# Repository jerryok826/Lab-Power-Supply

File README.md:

# Lab Power Supply

## Project Description
I always thought that most laborary power supplies (LPS) take up to much bench space. This design is just 2.5 inches by 5.5 inches and runs off a wall wart or it can be powered from a lithium battery pack. The unit's specs are 0 to 15 volts output with a maximum output current of 1.5 amps. It has two output adjustable voltage presets with defaults of 5 and 3.3 volts. It has two rotary encoders, one for voltage control and the other for current limiting. Pressing an encoder button will change it's adjustement range. There is one additional button for output enable. The LPS can also be controlled remotely via USB using ModBus. There is also a realtime analog current bar graph on the oled display.

The control processor is a stm32f103c8t6, an Arm Cortex-M3 MCU with 64 Kbytes of flash memory and a 72 MHz CPU. The current code runs on libopencm3 and FreeRTOS. The display is a 256x128 OLED display. It is driven by uGui software. The unit is composed of two boards. The top board is the control and display board. The board below is the regulator board. The regulator board is composed of a low voltage drop linear regulator and a highly efficient switching regulator. Because of the combined efficiency of the switching and linear regulator not much of a heat sink is required. To reduce the noise generated by the switcher to a minimum, the switcher has large imput capacitors and a 3KHz loop pass filter on its output feeding the linear regulator. The switcher output voltage set to maintain a two voltage drop across the linear regulator.
### Project Status
The project is basically complete. I am working on converting the design to Kicad and STM32 IDE Cube. Also I'm thinking abouting redoing the display board with a RP2040 running MicroPython. This should make it easy for the end user to add their own features. For example, adding WIFI control support.

## Design Files
### Electrical Design Files
This project was initially designed with Altium Designer and is now being updated with Kicad 7.X The control software is C code runing on FreeRTOS.

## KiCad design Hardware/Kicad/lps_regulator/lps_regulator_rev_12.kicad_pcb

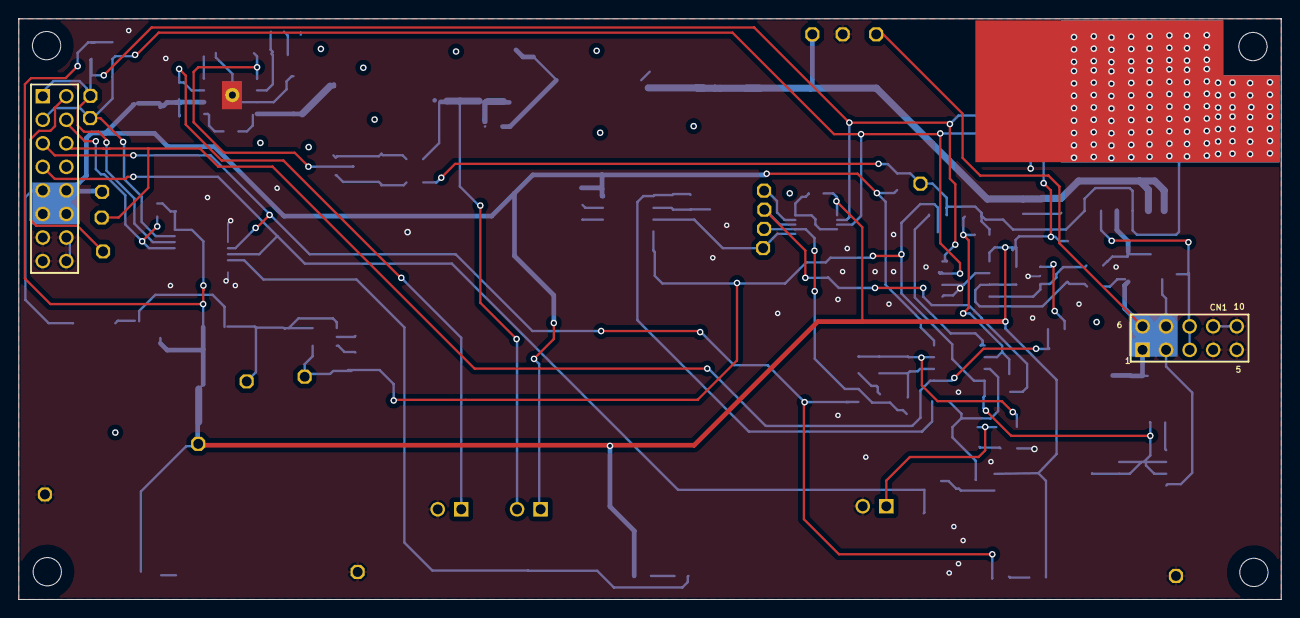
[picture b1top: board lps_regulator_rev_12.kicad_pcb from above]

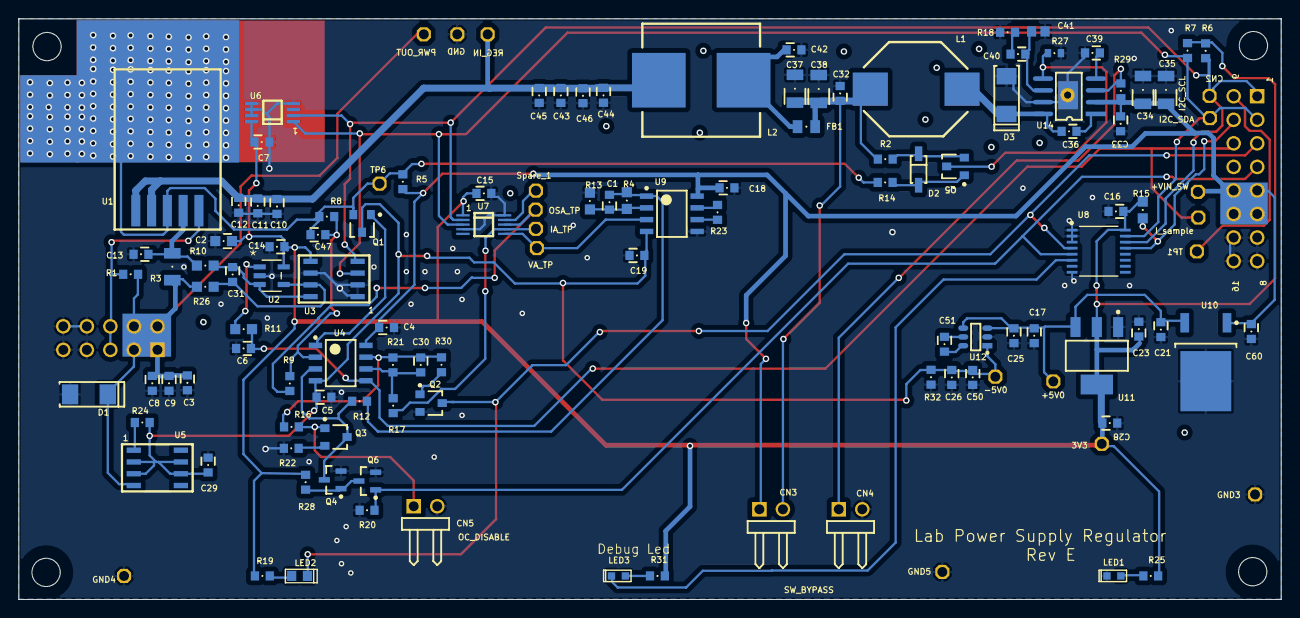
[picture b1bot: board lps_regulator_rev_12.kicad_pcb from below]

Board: 2 copper layers, 136.2 x 62.6 mm, 130 parts (109 on the bottom side), 55 nets.

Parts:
3V3: TestPoint_BLK; TestPoint-TH 42 mil
+5V0: TestPoint_BLK; TestPoint-TH 42 mil
+VIN_SW: TestPoint_BLK; TestPoint-TH 42 mil
-5V0: TestPoint_BLK; TestPoint-TH 42 mil
C1: 100pF; CAPC0603(1608)_N
C2: 0.1uF; CAPC0603(1608)_M
C3, C4, C5, C7, C12, C13, C14, C15, C16, C18, C19, C21, C23, C26, C29, C31, C32, C36, C42, C44, C47: 0.1uF; CAPC0603(1608)_N
C6, C8, C9, C10, C11, C17, C25, C28, C30, C43, C45, C50: 10uF; CAPC0603(1608)_N
C33, C39: 0.01uF; CAPC0603(1608)_N
C34, C35: 4.7uF; CAPC1206(3216)_N
C37, C38: 47UF; CAPC1206(3216)_N
C40: 150pF; CAPC0603(1608)_N
C41: 8.2nF; CAPC1608X87X35ML15T15
C46, C51, C60: 1uF; CAPC0603(1608)_N
CN1: Header 5X2A; HDR2X5_CEN
CN2: Header 8X2A; HDR2X8_CEN
CN3, CN4, CN5: Header 2H; HDR1X2H
D1, D3: B340A; DO-214AC
D2: 1N4448W-E3-18; SOD123
FB1: 300 Ohm @ 100MHz, 0805; RESC0805(2012)_N
GND, GND3, GND4, GND5: TestPoint_BLK; TestPoint-TH 42 mil
I2C_SCL, I2C_SDA: TestPoint_BLK; TestPoint-TH 42 mil
IA_TP: TestPoint_BLK; TestPoint-TH 42 mil
I_sample: TestPoint_BLK; TestPoint-TH 42 mil
L1: SSR1028 6.8uH; SRU1028
L2: SSR1210 100uH; SRR1210
LED1, LED3: 0603 LED; SM-LED-0603
LED2: G; SM-LED-0603
OSA_TP: TestPoint_BLK; TestPoint-TH 42 mil
PWR_OUT: TestPoint_BLK; TestPoint-TH 42 mil
Q1, Q5: MMBT2907A; SOT23
Q2, Q3: MMBT3904; SOT23
Q4, Q6: BSS123TA; SOT23-3L
R1, R23, R24: 100; RESC0603(1608)_N
R2, R5, R6, R7, R8, R9, R14, R20, R28, R29: 10K; RESC0603(1608)_N
R3: 0.33; RESC1206(3216)_N
R4, R13, R15: 10k; RESC0603(1608)_M
R10, R11, R26: 10K; RESC0603(1608)_M
R12, R16, R17, R19, R22, R25, R30, R31, R32: 1.0K; RESC0603(1608)_N
R18: 33K; RESC0603(1608)_N
R21: 100K; RESC0603(1608)_N
R27: 10K; RESC0603(1608)_L
REG_IN: TestPoint_BLK; TestPoint-TH 42 mil
Spare_1: TestPoint_BLK; TestPoint-TH 42 mil
TP1, TP6: TestPoint_BLK; TestPoint-TH 42 mil
U1: TPS7A4515KTTR
U2: INA180A1; SOT-23-5_MC
U3: INA219
U4, U9: OPA2320; SOIC-8_NoPad
U5: LM334
U6: mcp9808; 8MSOP
U7: mcp4728; MCP4728
U8: TCA9534APWR; TCA9534APWR-Footprint-1
U10: TO-252_N
U11: LD1117S33; DSO-G3
U12: LM2776; SOt-23-6
U14: TPS54331
VA_TP: TestPoint_BLK; TestPoint-TH 42 mil

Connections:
3V3: 3V3.1, C2.1, C7.1, C14.1, C15.1, C16.1, C23.1, C28.1, R6.1, R7.1, R15.2, R19.1, R25.1, R28.1, R31.1, U2.5, U3.5, U6.8, U7.1, U8.16, U11.2, U11.4
+5V0: +5V0.1, C17.1, C21.1, C25.1, U10.3, U11.3, U12.3, U12.4
+VIN_SW: +VIN_SW.1, C4.1, C18.1, C33.1, C34.1, C35.1, C60.1, CN2.5, CN2.6, CN2.13, CN2.14, CN3.1, R5.1, R29.1, U4.8, U9.8, U10.1, U14.2
-5V0: -5V0.1, C5.1, C19.2, C26.1, C29.2, C50.1, Q1.3, R24.2, R32.1, U4.4, U5.2, U5.3, U5.6, U5.7, U9.4, U12.1
/INT: CN2.10, R15.1, U8.13
/RST: CN2.9, TP1.1
Current_Limit: CN2.3, LED2.2, Q2.3, U8.4
Debug_LED: LED3.2, U8.6
GND: C2.2, C3.2, C4.2, C5.2, C6.2, C7.2, C8.2, C9.2, C10.2, C11.2, C12.2, C13.2, C14.2, C15.2, C16.2, C17.2, C18.2, C19.1, C21.2, C23.2, C25.2, C26.2, C28.2, C29.1, C32.2, C33.2, C34.2, C35.2, C37.2, C38.2, C39.2, C41.1, C42.2, C43.2, C44.2, C45.2, C46.2, C50.2, C60.2, CN1.4, CN1.5, CN1.9, CN1.10, CN2.7, CN2.8, CN2.15, CN2.16, CN4.2, CN5.2, D1.1, D3.1, GND.1, GND3.1, GND4.1, GND5.1, LED1.2, Q2.2, Q4.2, Q6.2, R13.1, R18.2, R20.2, R22.2, R27.2, R32.2, U2.2, U3.1, U3.2, U3.6, U6.4, U6.5, U6.6, U6.7, U7.4, U7.10, U8.1, U8.2, U8.3, U8.8, U9.5, U10.4, U11.1, U12.2, U14.7, U14.9
I2C_SCL: CN2.1, I2C_SCL.1, R6.2, U3.4, U6.2, U7.2, U8.14
I2C_SDA: CN2.2, I2C_SDA.1, R7.2, U3.3, U6.1, U7.3, U8.15
IA_TP: IA_TP.1, R17.1, U7.7
I_Sample: C6.1, CN2.11, I_sample.1, R11.2, U4.5
NetC1_1: C1.1, R4.1, R13.2, U9.2
NetC17_1: C51.1, U12.5
NetC17_2: C51.2, U12.6
NetC30_1: C30.1, R16.1, R21.2, R30.2, U4.7
NetC30_2: C30.2, R17.2, R21.1, U4.6
NetC31_1: C31.1, R10.1, U2.3, U3.8
NetC31_2: C31.2, R26.1, U2.4, U3.7
NetC32_1: C32.1, C37.1, C38.1, CN3.2, FB1.1, L1.2, R2.1
NetC36_1: C36.1, U14.1
NetC36_2: C36.2, D3.2, L1.1, U14.8
NetC39_1: C39.1, U14.4
NetC40_1: C40.1, C41.2, U14.6
NetC40_2: C40.2, R18.1
NetC42_1: C42.1, FB1.2, L2.1
NetC47_1: C47.1, Q1.2, R5.2, R8.1, R14.2, TP6.1, U1.3, U1.6
NetC47_2: C47.2, R8.2, R9.1, U4.2
NetCN1_3: CN1.3, CN1.8, R1.2, U1.5
NetCN4_1: CN4.1, R29.2, U14.3
NetCN5_1: CN5.1, Q3.1, R16.2
NetD2_1: D2.1, Q5.1, R14.1
NetD2_2: D2.2, Q5.2, R2.2
NetLED1_1: LED1.1, R25.2
NetLED2_1: LED2.1, R19.2
NetLED3_1: LED3.1, R31.2
NetQ1_1: Q1.1, U4.1
NetQ2_1: Q2.1, R30.1
NetQ3_2: Q3.2, R22.1
NetQ3_3: Q3.3, Q4.3, R12.2, U4.3
NetQ4_1: Q4.1, Q6.3, R28.2
NetQ5_3: Q5.3, R27.1, U14.5
NetR11_1: R11.1, U2.1
NetR23_1: R23.1, U9.6
NetR23_2: R23.2, U9.7
NetR24_1: R24.1, U5.1
NetSpare_1_1: Spare_1.1, U7.9
OUTPUT_ENB: CN2.4, Q6.1, R20.1, U8.5
Pwr_Out: C3.1, C8.1, C9.1, CN1.1, CN1.2, CN1.6, CN1.7, D1.2, PWR_OUT.1, R1.1, R3.2, R26.2, U5.4
Pwr_Out_Sample: C13.1, R3.1, R10.2, U1.4
REG_VIN: C10.1, C11.1, C12.1, C43.1, C44.1, C45.1, C46.1, L2.2, REG_IN.1, U1.1, U1.2
VA_TP: U7.6, U9.3, VA_TP.1
VA_TP_GAIN: C1.2, R4.2, R12.1, U9.1
V_offset_adj: OSA_TP.1, R9.2, U7.8

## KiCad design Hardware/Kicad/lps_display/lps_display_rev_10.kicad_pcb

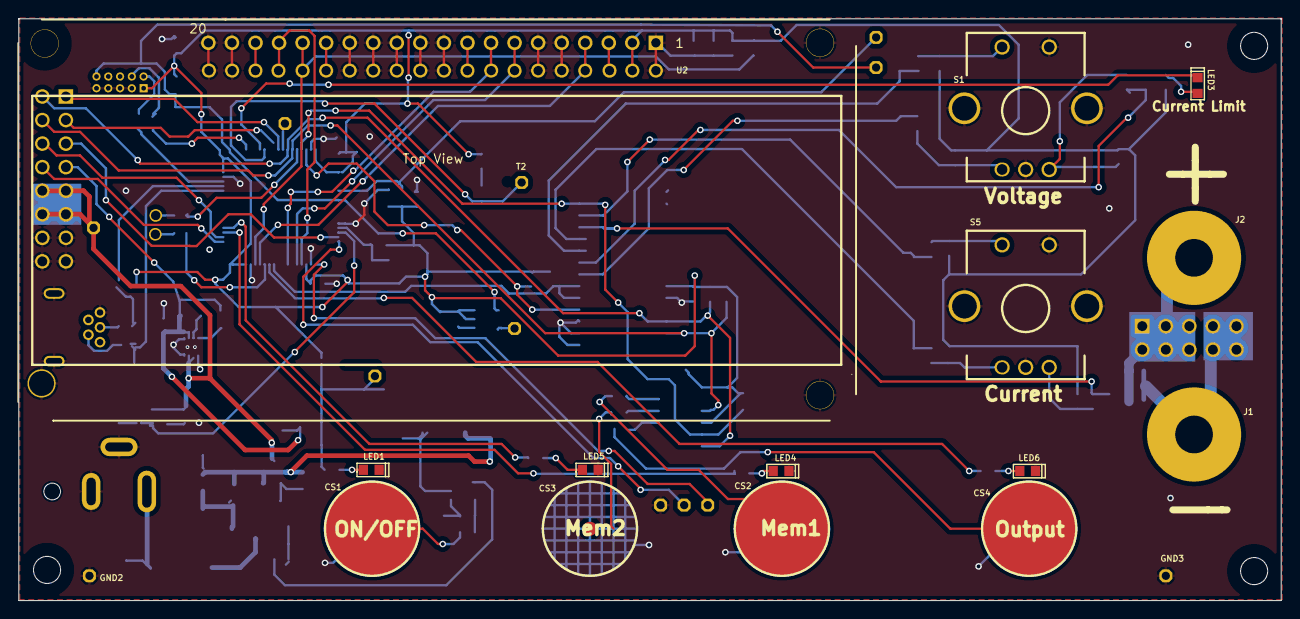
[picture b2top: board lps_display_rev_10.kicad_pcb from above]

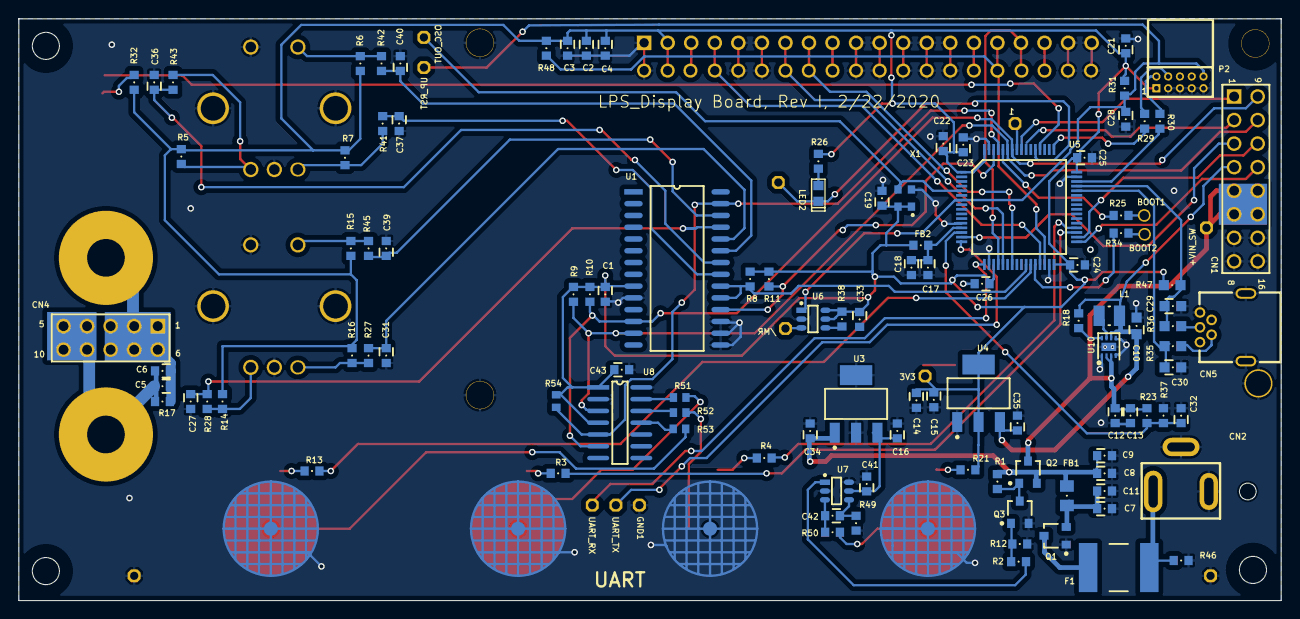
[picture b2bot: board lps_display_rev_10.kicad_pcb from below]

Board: 2 copper layers, 136.1 x 62.7 mm, 137 parts (112 on the bottom side), 84 nets.

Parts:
1, 3V3: TestPoint-TH 35 mil
+VIN_SW: TestPoint-TH 35 mil
/MR: TestPoint-TH 35 mil
BOOT1, BOOT2: TP; TestPoint-TH 40 mil
C1, C4, C6, C8, C11, C13, C15, C18, C19, C21, C23, C24, C25, C26, C27, C31, C32, C33, C34, C35, C36, C37, C39, C40, C41, C42, C43: 0.1uF 0603 50V; CAPC0603(1608)_N
C2, C3, C5, C7, C9, C12, C14, C16, C17, C22: 10uF; CAPC0603(1608)_N
C10: 22uF; CAPC0603(1608)_M
C28: 1uF; CAPC0603(1608)_N
C29, C30: 33pF; CAPC0603(1608)_M
CN1: Header 8X2A; HDR2X8_CEN
CN2: PJ-050AH
CN4: Header 5X2A; HDR2X5_CEN
CN5: Mini-USB RA Type B; USB-MINI-B - 2A
CS1, CS2, CS3, CS4: Cap_Sense_Pad; CAP_TOUCH_ROUND
F1: 2920L500/16MR; 2920 Fuse
FB1: 300 Ohm @ 100MHz, 0806; RESC0805(2012)_M
FB2: BLM18RK601SN1D; RESC0603(1608)_N
GND1, GND2, GND3: TestPoint-TH 35 mil
J1, J2: banana_jack1; Banana_jack1
L1: 2.2uH; INDC2520X10N
LED1, LED2, LED3, LED4, LED5, LED6: G; SM-LED-0603
OSC_OUT: TestPoint-TH 35 mil
P2: jtag_debug
Q1, Q2: DMP3099L-7; SOT23
Q3: MMBT3904; SOT23
R1, R2, R5, R6, R7, R8, R9, R10, R11, R12, R14, R15, R16, R17, R21, R27, R28, R38, R41, R42, R43, R45, R48: 4.7K; RESC0603(1608)_N
R3, R4, R13, R23, R26, R32, R37, R46, R49, R50: 1.0K; RESC0603(1608)_N
R18, R25, R34: 100K; RESC0603(1608)_N
R29, R30: 100; RESC0603(1608)_N
R31: 10K 1%; RESC0603(1608)_N
R35, R36: 22; RESC0603(1608)_M
R47: 1.54K; RESC0603(1608)_M
R51, R52, R53, R54: 5.1K; RESC1608X55X30NL15T15
S1, S5: rotary encoder
T2: TestPoint-TH 35 mil
U1: MCP23017; SOIC28
U2: OLED Display; oled_graphic_256X64
U3: TPS7B6933QDCYRQ1; SOT-223
U4: 3.3V; DSO-G3
U5: STM32F103RCT6; LQFP64
U6: TPS3808G33; SOt-23-6
U7: AT42QT1012; SOt-23-6
U8: AT42QT1070; SOP14
U10: TPS62173DSGT; WSON(8) 2mm x 2mm
UART_RX: TestPoint-TH 35 mil
UART_TX: TestPoint-TH 35 mil
UP_RST: TestPoint-TH 35 mil
X1: 8.0000MHZ; ECS-TXO-2520-33-160-AN-TR-Footprint-1

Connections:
3V3: 3V3.1, C1.1, C2.1, C3.1, C4.1, C14.1, C15.1, C19.1, C21.1, C22.1, C23.1, C24.1, C25.1, C26.1, C33.1, C43.1, FB2.1, P2.1, R5.2, R6.2, R7.2, R8.2, R9.2, R10.2, R11.2, R14.2, R15.2, R16.2, R21.2, R26.2, R31.1, R32.2, R38.2, R47.1, R48.2, R54.2, U1.9, U2.2, U4.2, U4.4, U5.1, U5.19, U5.32, U5.48, U5.64, U6.5, U6.6, U8.1, U8.4, X1.1, X1.4
5V0: C10.1, C35.1, CN1.4, L1.2, R18.1, U4.3, U10.6
8MH_XTAL_IN: OSC_OUT.1, U5.5, X1.3
+VIN: C8.1, C9.1, C34.1, FB1.2, Q2.2, R1.2, U3.1
+VIN_SW: +VIN_SW.1, C12.1, C13.1, CN1.5, CN1.6, CN1.13, CN1.14, Q2.3, R23.2, U10.2, U10.3
/CAP_T_INT: R54.1, U1.27, U5.61, U8.5
/INT: R8.1, U1.19, U1.20, U5.26
/RST_MCP23017: R11.1, U1.18, U5.62
/RST_OLED: R48.1, U2.16, U5.30
Current_Limit: CN1.11, U5.34
D/C_OLED: U2.4, U5.29
DEBUG_LED: LED2.2, T2.1, U5.53
GND: C1.2, C2.2, C3.2, C4.2, C7.2, C8.2, C9.2, C10.2, C11.2, C12.2, C13.2, C14.2, C15.2, C16.2, C17.2, C18.2, C19.2, C21.2, C22.2, C23.2, C24.2, C25.2, C26.2, C27.2, C28.2, C29.2, C30.2, C31.2, C32.2, C33.2, C34.2, C35.2, C36.2, C37.2, C39.2, C40.2, C41.2, C43.2, CN1.7, CN1.8, CN1.15, CN1.16, CN2.2, CN2.3, CN5.0, CN5.5, CS1.2, CS2.2, CS3.2, CS4.2, GND1.1, GND2.1, GND3.1, LED1.2, LED4.2, LED5.2, LED6.2, P2.3, P2.5, P2.7, P2.9, Q1.1, Q3.2, R12.2, R37.1, R46.1, R49.1, S1.2, S1.4, S1.5, S1.7, S5.2, S5.4, S5.5, S5.7, U1.10, U1.15, U1.16, U1.17, U2.1, U2.5, U2.6, U2.10, U2.11, U2.12, U2.13, U2.14, U2.19, U2.20, U3.2, U3.4, U4.1, U5.12, U5.18, U5.31, U5.47, U5.63, U6.2, U7.2, U7.6, U8.2, U8.14, U10.1, U10.4, U10.5, U10.9, X1.2
I2C_SCL: CN1.9, R10.1, U1.12, U5.58, U8.6
I2C_SDA: CN1.10, R9.1, U1.13, U5.59, U8.3
I_ENC_A: C31.1, R27.2, U1.24
I_ENC_B: C27.1, R28.2, U1.25
I_ENC_SW: C39.1, R45.1, U1.26
I_Sample: CN1.3, U5.15
MEM1_LED: R3.1, U5.35
MEM2_LED: R4.1, U5.36
NRST: C28.1, P2.10, R31.2, U5.7, U6.1, UP_RST.1
Net1_1: 1.1, U5.57
Net/MR_1: /MR.1, U6.3
NetBOOT1_1: BOOT1.1, R25.1
NetBOOT2_1: BOOT2.1, R34.2
NetC5_1: C5.1, C6.1, CN4.1, CN4.2, CN4.3, CN4.6, CN4.7, CN4.8, J2.1, R17.2
NetC5_2: C5.2, C6.2, CN4.4, CN4.5, CN4.9, CN4.10, J1.1, R17.1
NetC7_1: C7.1, C11.1, FB1.1, Q1.2
NetC16_1: C16.1, C41.1, U3.3, U7.5
NetC17_1: C17.1, C18.1, FB2.2, U5.13
NetC42_1: C42.1, R49.2, U7.4
NetC42_2: C42.2, R50.2, U7.3
NetCN2_1: CN2.1, F1.1, R46.2
NetCN5_2: CN5.2, R35.1
NetCN5_3: CN5.3, R36.1
NetCS1_1: CS1.1, R50.1
NetCS2_1: CS2.1, R51.2
NetCS3_1: CS3.1, R52.2
NetCS4_1: CS4.1, R53.2
NetF1_2: F1.2, Q1.3
NetL1_1: L1.1, U10.7
NetLED1_1: LED1.1, R21.1
NetLED2_1: LED2.1, R26.1
NetLED3_1: LED3.1, R32.1
NetLED4_1: LED4.1, R3.2
NetLED5_1: LED5.1, R4.2
NetLED6_1: LED6.1, R13.2
NetP2_2: P2.2, R30.1
NetP2_4: P2.4, R29.1
NetQ2_1: Q2.1, Q3.3, R1.1
NetQ3_1: Q3.1, R2.1, R12.1
NetR2_2: R2.2, U7.1
NetR5_1: R5.1, R43.1, S1.3
NetR6_1: R6.1, R42.2, S1.6
NetR7_1: R7.1, R41.1, S1.1
NetR14_1: R14.1, R28.1, S5.3
NetR15_1: R15.1, R45.2, S5.6
NetR16_1: R16.1, R27.1, S5.1
NetR18_2: R18.2, U10.8
NetR25_2: R25.2, U5.60
NetR34_1: R34.1, U5.28
NetR38_1: R38.1, U6.4
NetR51_1: R51.1, U8.13
NetR52_1: R52.1, U8.12
NetR53_1: R53.1, U8.11
OC_LED: LED3.2, U5.52
OUTPUT_ENB: CN1.12, U5.33
OUTPUT_LED: R13.1, U5.27
SPI_MOSI_1: U2.8, U5.23
SPI_NSS_1: U2.17, U5.20
SPI_SCK_1: U2.7, U5.21
Spare1: CN1.2, U5.55
Spare2: CN1.1, U5.56
TCK/SWDCLK: R29.2, U5.49
TMS/SWDIO: R30.2, U5.46
UART_RX_2: U5.17, UART_RX.1
UART_TX_2: U5.16, UART_TX.1
USBDM: C30.1, R35.2, U5.44
USBDP: C29.1, R36.2, R47.2, U5.45
VIN_CHK: C32.1, R23.1, R37.2, U5.14
V_ENC_A: C37.1, R41.2, U1.21
V_ENC_B: C36.1, R43.2, U1.22
V_ENC_SW: C40.1, R42.1, U1.23

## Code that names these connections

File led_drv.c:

/* main.c : Lab Power Supply 
 */
#include <stdlib.h>
#include <string.h>
#include <stdbool.h>
#include <ctype.h>
#include <stdint.h>

#include <libopencm3/stm32/rcc.h>
#include <libopencm3/stm32/gpio.h>
#include <libopencm3/stm32/adc.h>
#include <libopencm3/stm32/spi.h>
#include <libopencm3/stm32/exti.h>
#include <libopencm3/cm3/nvic.h>
#include <libopencm3/cm3/systick.h>
#include <libopencm3/stm32/iwdg.h>

#include "FreeRTOS.h"
#include "task.h"
#include "semphr.h"
#include "mcuio.h"
#include "led_drv.h"

// indent -gnu -br -cli2 -lp -nut -l100 led_drv.c 

typedef struct _led_db
{
  uint32_t port;
  uint32_t bit;
  uint32_t invert;
} led_db_t;

#define OUTPUT_LED 0
#define MEM1_LED   1
#define MEM2_LED   2
#define DEBUG_LED  3
#define OC_LED     4

led_db_t led[] = {
  {GPIOB, GPIO1, 1},            // OUTPUT_LED
  {GPIOB, GPIO14, 1},           // MEM1_LED
  {GPIOB, GPIO15, 1},           // MEM2_LED
  {GPIOC, GPIO12, 0},           // DEBUG_LED
  {GPIOC, GPIO11, 0},           // OC_LED
};

void
led_setup (int led_nub)
{
  if (led_nub < LED_MAX) {
    gpio_set_mode (led[led_nub].port, GPIO_MODE_OUTPUT_50_MHZ, GPIO_CNF_OUTPUT_PUSHPULL,
                   led[led_nub].bit);
  }
  led_off (led_nub);
}

void
led_all_setup (void)
{
  int idx = 0;
  for (idx = 0; (idx < LED_MAX); idx++) {
    led_setup (idx);
  }
}

void
led_on (int led_nub)
{
  if (led_nub < LED_MAX) {
    if (led[led_nub].invert) {
      gpio_set (led[led_nub].port, led[led_nub].bit);
    }
    else {
      gpio_clear (led[led_nub].port, led[led_nub].bit);
    }
  }
}

void
led_all_on (void)
{
  int idx = 0;
  for (idx = 0; (idx < LED_MAX); idx++) {
    led_on (idx);
  }
}

void
led_off (int led_nub)
{
  if (led_nub < LED_MAX) {
    if (led[led_nub].invert) {
      gpio_clear (led[led_nub].port, led[led_nub].bit);
    }
    else {
      gpio_set (led[led_nub].port, led[led_nub].bit);
    }
  }
}

void
led_all_off (void)
{
  int idx = 0;
  for (idx = 0; (idx < LED_MAX); idx++) {
    led_off (idx);
  }
}

void
led_toggle (int led_nub)
{
  if (led_nub < LED_MAX) {
    gpio_toggle (led[led_nub].port, led[led_nub].bit);
  }
}

void
led_all_toggle (void)
{
  int idx = 0;
  for (idx = 0; (idx < LED_MAX); idx++) {
    led_toggle (idx);
  }
}

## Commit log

2020-10-19 inital commit
2020-10-19 add photos
2020-10-27 add hardware projects
2020-10-28 reorg
2020-10-28 clean up
2020-10-28 add hw library and display hw
2020-11-01 update pictures
2024-02-23 code clean up and add kicad hw work
2024-02-28 add current reg sch
2024-02-29 update picture
2024-03-27 add stm32 cude support
2024-03-27 add stm32 cube support
2024-03-27 old code clean out
2026-03-24 added missing .cproject
2026-03-24 serial port log
2026-03-24 Add missing .cproject file
2026-03-24 Add some missing files
